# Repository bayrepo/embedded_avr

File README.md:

# embedded_avr

**Examples of code for avr controllers**

* attiny13a/uart_program - пример, как добавить передачу передачу данных с МК attiny13a по UART на скорости 9600 (пример собран c источников: https://habr.com/ru/post/250995/ и http://we.easyelectronics.ru/AVR/uart-programmnyy-na-atiny13a.html)
* attiny45/i2c_slave - пример программного i2c протокола для контроллера attiny45
* atmega8/monitor_i2c_uart - программа, по выводу информации с источников подключаемых по i2c и по UART для МК ATmega8
* attiny13a/joystyk_transmitter_attiny13a - программа для опроса джойстика и посылки информации с джойстика по радиоканалу. На основе кода https://github.com/cano64/ManchesterRF
* attiny45/joystyk_reciver_attiny45 - программа приема информации с джойстика и управление серводвигателями на сонове полученной ифнормации, на основе кода https://github.com/cano64/ManchesterRF
* atmega8/power_manager_transmitter - программа и схема передатчика управления питанием для статьи ...
* atmega8/power_manager_receiwer - программа и схема приемника управления питанием для статьи ...
* atmega8/button_on_the_interrupt - программа для Atmel Studio, где кнопка с апаратным подавлением шумов присоединяется к пину PD2 (INT0) и нажатие кнопки осуществляется по прерывнию.
* atmega8/microscope_management - программа для управления приводом стола, подсветкой микроскопа, а также схема в KiCAD и 3д-модели для принтера из которых микроскоп собирался. Интересные моменты - это обработка кнопок на основании прерываний и считывание позиции потенциометра с помощью АЦП микроконтроллера.
* attiny13a/joystyk_motor_set_angle - программа для опроса джойстика и поворота двигателей на основе позиции джойстика. Угол наклона джойстика указывает на какой угол установить моторы.
* attiny13a/joystyk_motor_set_step - программа для опроса джойстика и поворота двигателей на основе позиции джойстика. Угол наклона джойстика указывает на какой шаг повернуть моторы.
* attiny13a/joystyk_motor_set_step_smooth - программа для опроса джойстика и поворота двигателей на основе позиции джойстика. Угол наклона джойстика указывает на какой шаг повернуть моторы. Движение серводвигателей более плавное.
* nomc/load - схема без МК, схема электронной нагрузки. В проекте KiCAD схема и плата, и модели для 3Д печати
* nomc/vrv600 - схема Sven VR V600.
* nomc/cnc3018 - модели для крепления лазера к станку и вентилятора, а так же модель коробочки для установки кнопок отключения вентилятора, шпинделя и кнопки сброса станка.
* attiny26l/sven_vrv600_avr - плата переходник, для использования AVR attiny26L в sven VRV600 стабилизаторе вместо Holtek микроконтрллера
* simavr/blink_c_for_testing - прошивка для attiny13a, для симуляции в simavr
* simavr/blink_c_for_testing_libsimavr - пример прошивки для attiny13a и пример программы для исследования работы прошивки и вывод изменений на выходах микроконтроллера в vcd файл
* simavr/sven600_simulation - симуляция в simavr ранее описанной прошивки для sven600. В данном случае в симуляторе реализована подача тестового входного сигнала на АЦП и организована визуальная проверка результата с помощью файла vcd.

Более детальная информация по проектам на [сайте](http://brepo.ru/)

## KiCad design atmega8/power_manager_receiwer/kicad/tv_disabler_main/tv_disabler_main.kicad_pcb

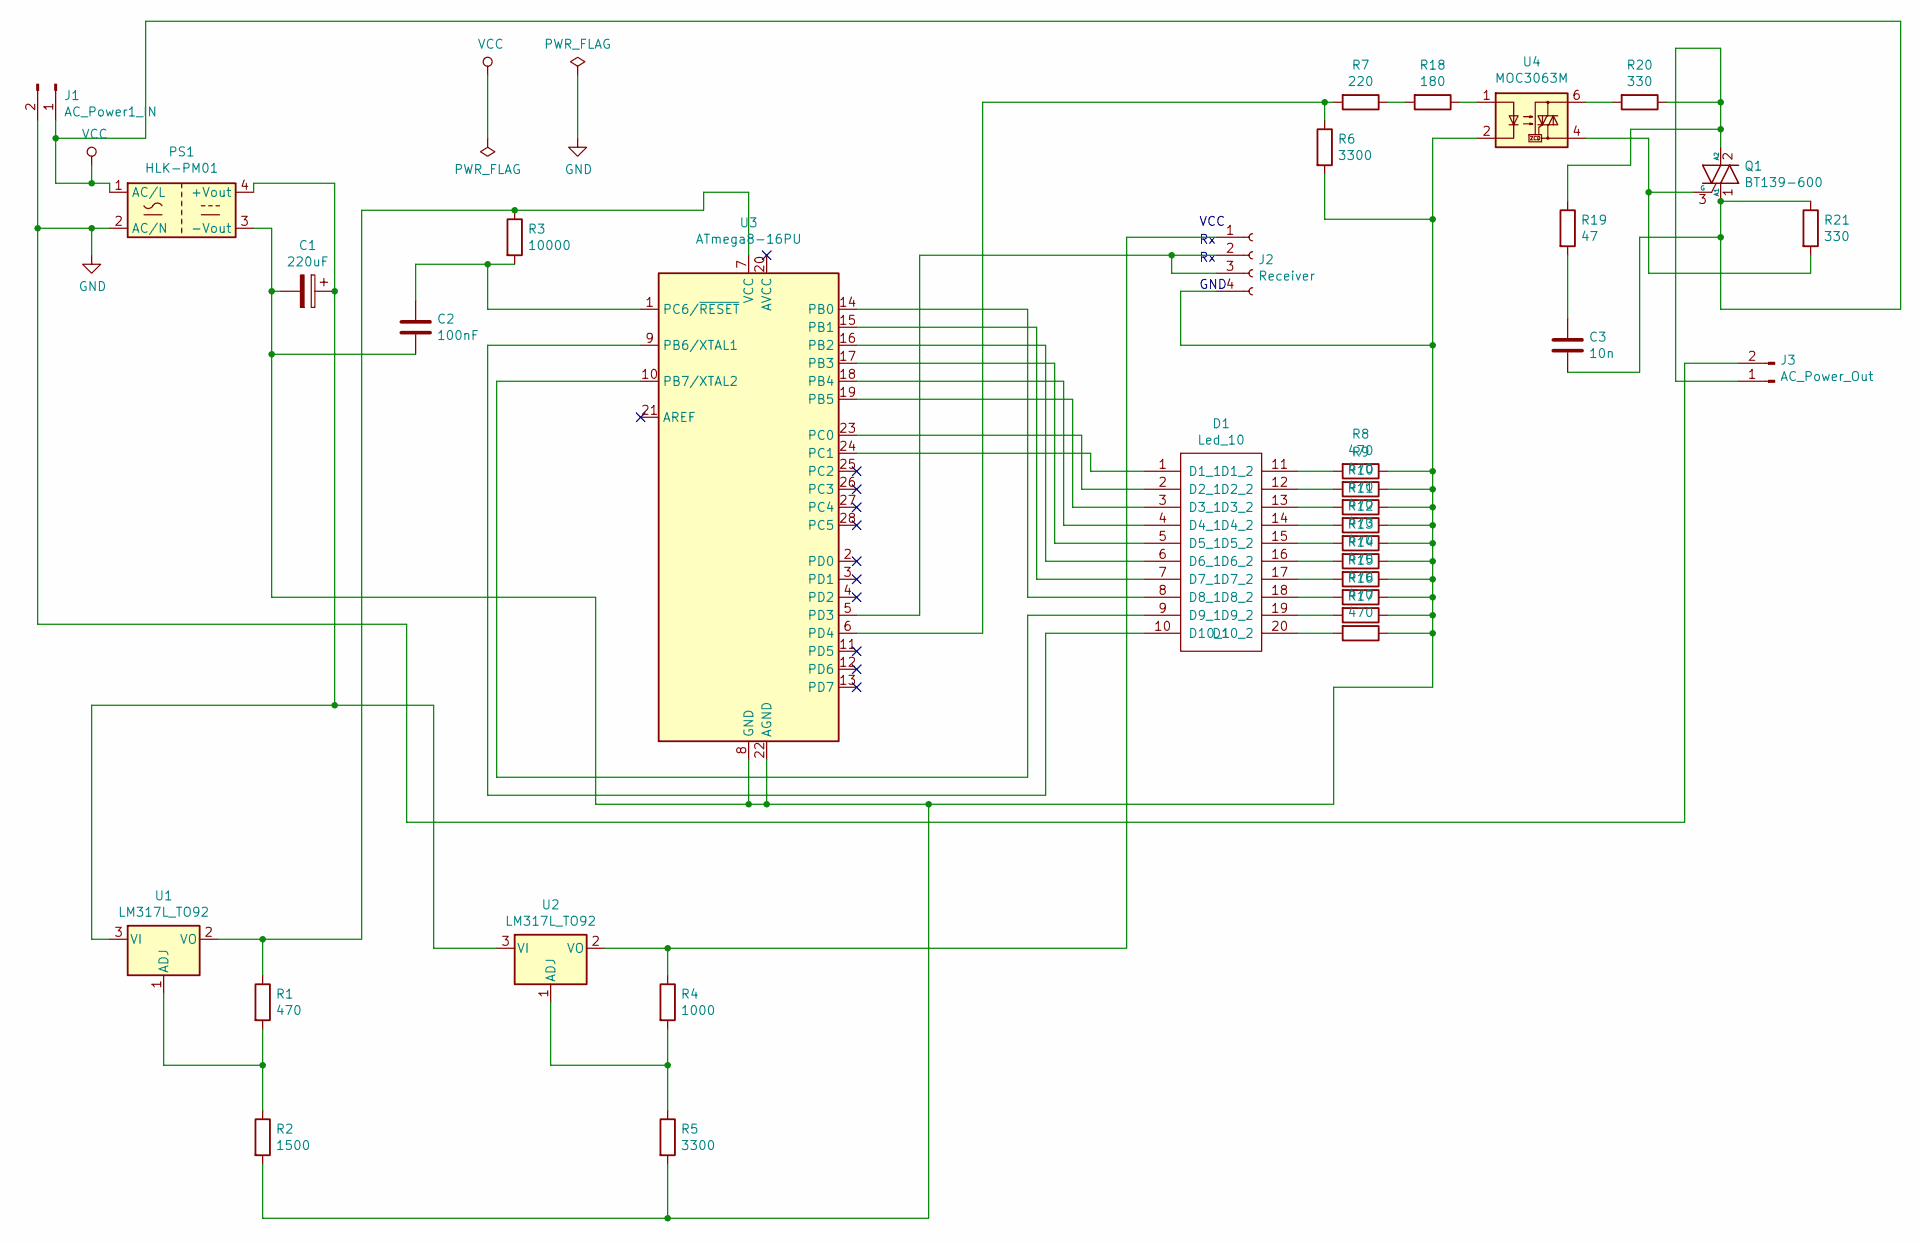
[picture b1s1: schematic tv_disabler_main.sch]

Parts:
C1: 220uF; CP_Radial_Tantal_D5.0mm_P5.00mm
C2: 100nF; C_Axial_L3.8mm_D2.6mm_P7.50mm_Horizontal
C3: 10n; C_Axial_L5.1mm_D3.1mm_P12.50mm_Horizontal
D1: Led_10; DIP-20_296_ELL
J1: AC_Power1_IN; 2-AC
J2: Receiver; SIP-4
J3: AC_Power_Out; 2-AC
PS1: HLK-PM01; ACDC-Conv_THTMeanWell-IRM-02-XX
Q1: BT139-600; TO-220-3_Vertical
R1, R8, R9, R10, R11, R12, R13, R14, R15, R16, R17: 470; R_Axial_DIN0207_L6.3mm_D2.5mm_P10.16mm_Horizontal
R2: 1500; R_Axial_DIN0207_L6.3mm_D2.5mm_P10.16mm_Horizontal
R3: 10000; R_Axial_DIN0207_L6.3mm_D2.5mm_P10.16mm_Horizontal
R4: 1000; R_Axial_DIN0207_L6.3mm_D2.5mm_P10.16mm_Horizontal
R5, R6: 3300; R_Axial_DIN0207_L6.3mm_D2.5mm_P10.16mm_Horizontal
R7: 220; R_Axial_DIN0207_L6.3mm_D2.5mm_P10.16mm_Horizontal
R18: 180; R_Axial_DIN0207_L6.3mm_D2.5mm_P10.16mm_Horizontal
R19: 47; R_Axial_Power_L50.0mm_W9.0mm_P55.88mm
R20, R21: 330; R_Axial_DIN0207_L6.3mm_D2.5mm_P10.16mm_Horizontal
U1, U2: LM317L_TO92; TO-252-2
U3: ATmega8-16PU; DIP-28_296_ELL
U4: MOC3063M; DIP-6_296_ELL

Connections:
GND: J1.2, J3.2, PS1.2 (AC/N)
unnamed: C1.1, PS1.4 (+Vout), U1.3 (VI), U2.3 (VI)
unnamed: C1.2, C2.2, J2.4, PS1.3 (-Vout), R2.2, R5.2, R6.2, R8.1, R9.1, R10.1, R11.1, R12.1, R13.1, R14.1, R15.1, R16.1, R17.1, U3.8 (GND), U3.22 (AGND), U4.2
unnamed: C2.1, R3.2, U3.1 (PC6/~RESET)
unnamed: C3.1, R19.2
unnamed: D1.1 (D1_1), U3.24 (PC1)
unnamed: D1.2 (D2_1), U3.23 (PC0)
unnamed: D1.3 (D3_1), U3.19 (PB5)
unnamed: D1.4 (D4_1), U3.18 (PB4)
unnamed: D1.5 (D5_1), U3.17 (PB3)
unnamed: D1.6 (D6_1), U3.16 (PB2)
unnamed: D1.7 (D7_1), U3.15 (PB1)
unnamed: D1.8 (D8_1), U3.14 (PB0)
unnamed: D1.9 (D9_1), U3.10 (PB7/XTAL2)
unnamed: D1.10 (D10_1), U3.9 (PB6/XTAL1)
unnamed: D1.11 (D1_2), R8.2
unnamed: D1.12 (D2_2), R9.2
unnamed: D1.13 (D3_2), R10.2
unnamed: D1.14 (D4_2), R11.2
unnamed: D1.15 (D5_2), R12.2
unnamed: D1.16 (D6_2), R13.2
unnamed: D1.17 (D7_2), R14.2
unnamed: D1.18 (D8_2), R15.2
unnamed: D1.19 (D9_2), R16.2
unnamed: D1.20 (D10_2), R17.2
unnamed: J2.1, R4.1, U2.2 (VO)
unnamed: J2.2, J2.3, U3.5 (PD3)
unnamed: J3.1, Q1.2 (A2), R19.1, R20.1
unnamed: Q1.3 (G), R21.2, U4.4
unnamed: R1.1, R3.1, U1.2 (VO), U3.7 (VCC)
unnamed: R1.2, R2.1, U1.1 (ADJ)
unnamed: R4.2, R5.1, U2.1 (ADJ)
unnamed: R6.1, R7.2, U3.6 (PD4)
unnamed: R18.1, U4.1
unnamed: R7.1, R18.2
unnamed: R20.2, U4.6
VCC: C3.2, J1.1, PS1.1 (AC/L), Q1.1 (A1), R21.1

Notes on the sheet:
VCC
GND

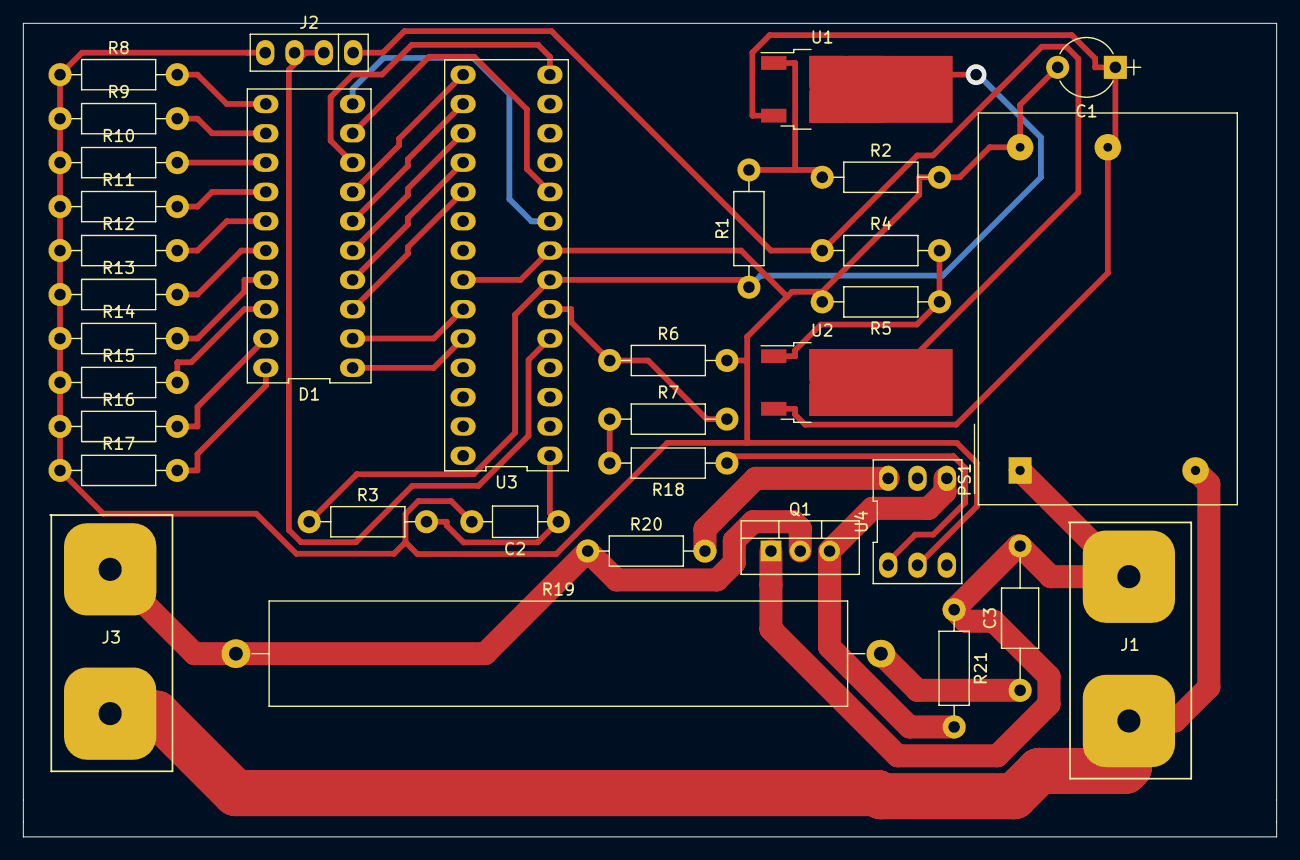
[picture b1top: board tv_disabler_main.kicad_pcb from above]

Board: 2 copper layers, 108.6 x 70.5 mm, 34 parts (0 on the bottom side), 37 nets.

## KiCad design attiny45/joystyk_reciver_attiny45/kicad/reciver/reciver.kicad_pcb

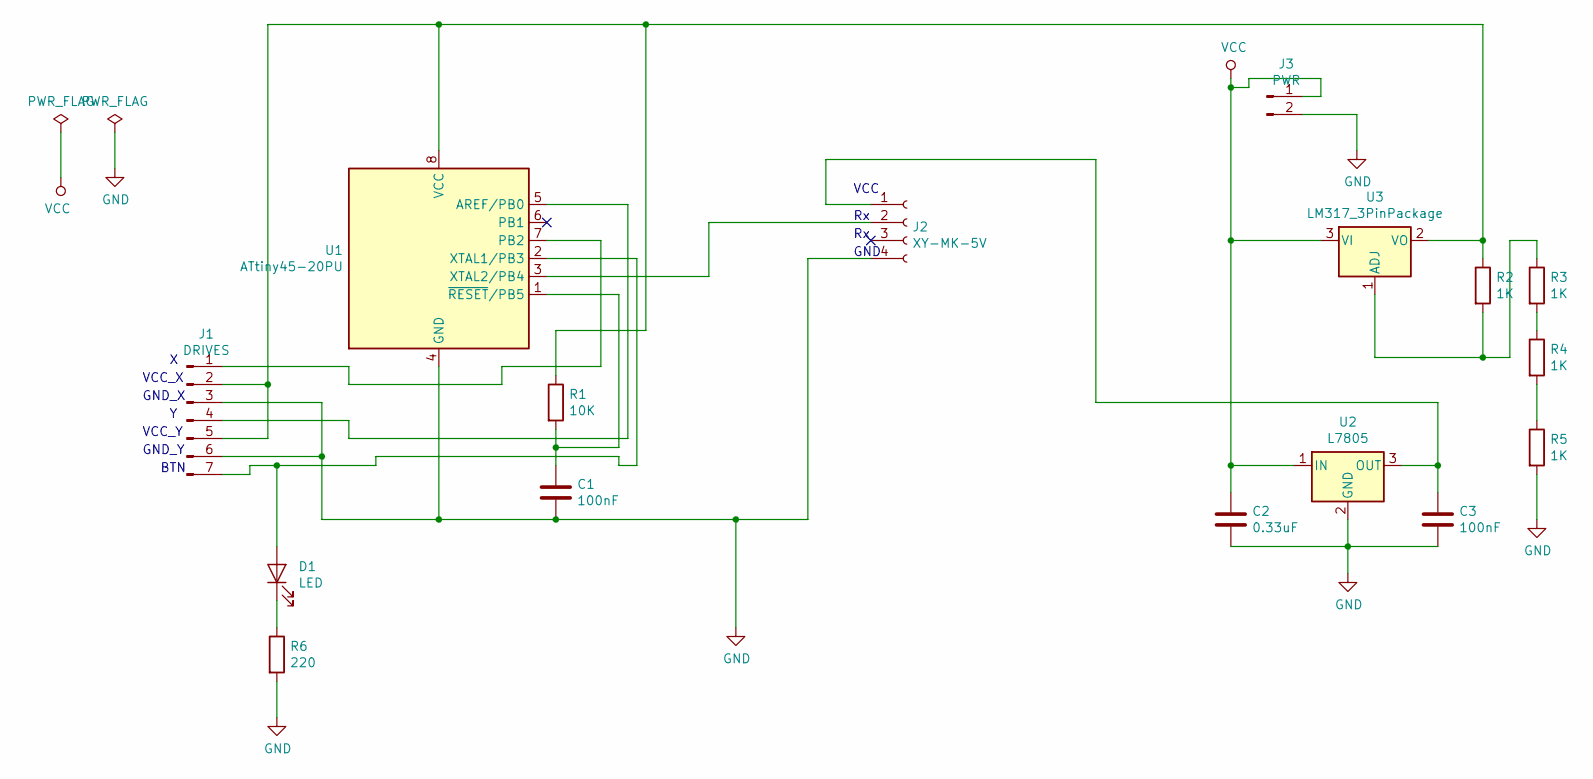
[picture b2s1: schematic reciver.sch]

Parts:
C1, C3: 100nF; R_my_5_08
C2: 0.33uF; R_my_5_08
D1: LED; R_my_5_08
J1: DRIVES; Socket_My_7_Pitch2.54mm
J2: XY-MK-5V; Socket_Strip_Straight_1x04_Pitch2.54mm
J3: PWR; Socket_2_My
R1: 10K; R_my_5_08
R2, R3, R4, R5: 1K; R_my_5_08
R6: 220; R_my_5_08
U1: ATtiny45-20PU; DIP-8_296
U2: L7805; Socket_3_My
U3: LM317_3PinPackage; Socket_3_My

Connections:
GND: C1.2, C2.2, C3.2, J1.3, J1.6, J2.4, J3.2, R5.2, R6.2, U1.4 (GND), U2.2 (GND)
unnamed: C1.1, R1.2, U1.1 (~RESET~/PB5)
unnamed: C3.1, J2.1, U2.3 (OUT)
unnamed: D1.1 (K), R6.1
unnamed: D1.2 (A), J1.7, U1.2 (XTAL1/PB3)
unnamed: J1.1, U1.7 (PB2)
unnamed: J1.2, J1.5, R1.1, R2.1, U1.8 (VCC), U3.2 (VO)
unnamed: J1.4, U1.5 (AREF/PB0)
unnamed: J2.2, U1.3 (XTAL2/PB4)
unnamed: R2.2, R3.1, U3.1 (ADJ)
unnamed: R3.2, R4.1
unnamed: R4.2, R5.1
VCC: C2.1, J3.1, U2.1 (IN), U3.3 (VI)

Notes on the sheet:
VCC
GND
VCC_X
GND_X
VCC_Y
GND_Y
BTN

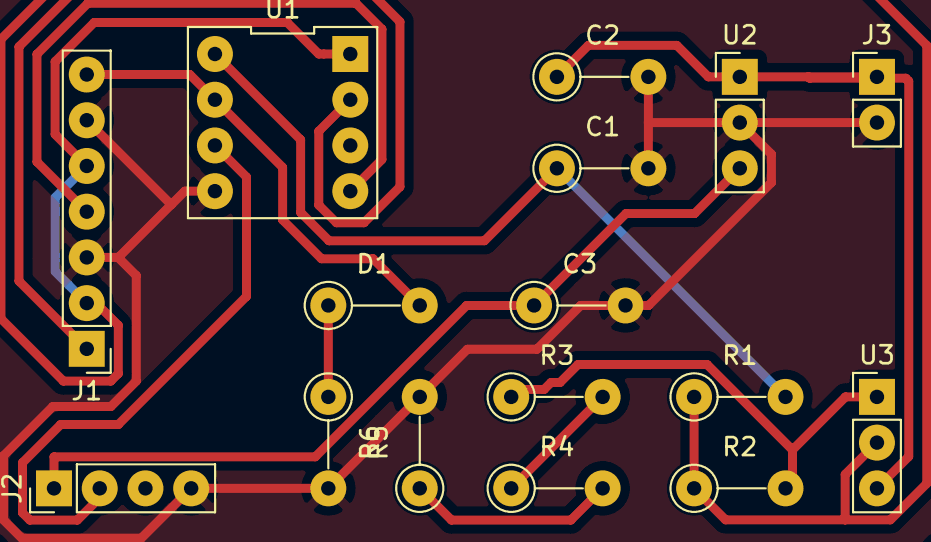
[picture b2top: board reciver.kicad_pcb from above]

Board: 2 copper layers, 16 parts (0 on the bottom side), 13 nets.

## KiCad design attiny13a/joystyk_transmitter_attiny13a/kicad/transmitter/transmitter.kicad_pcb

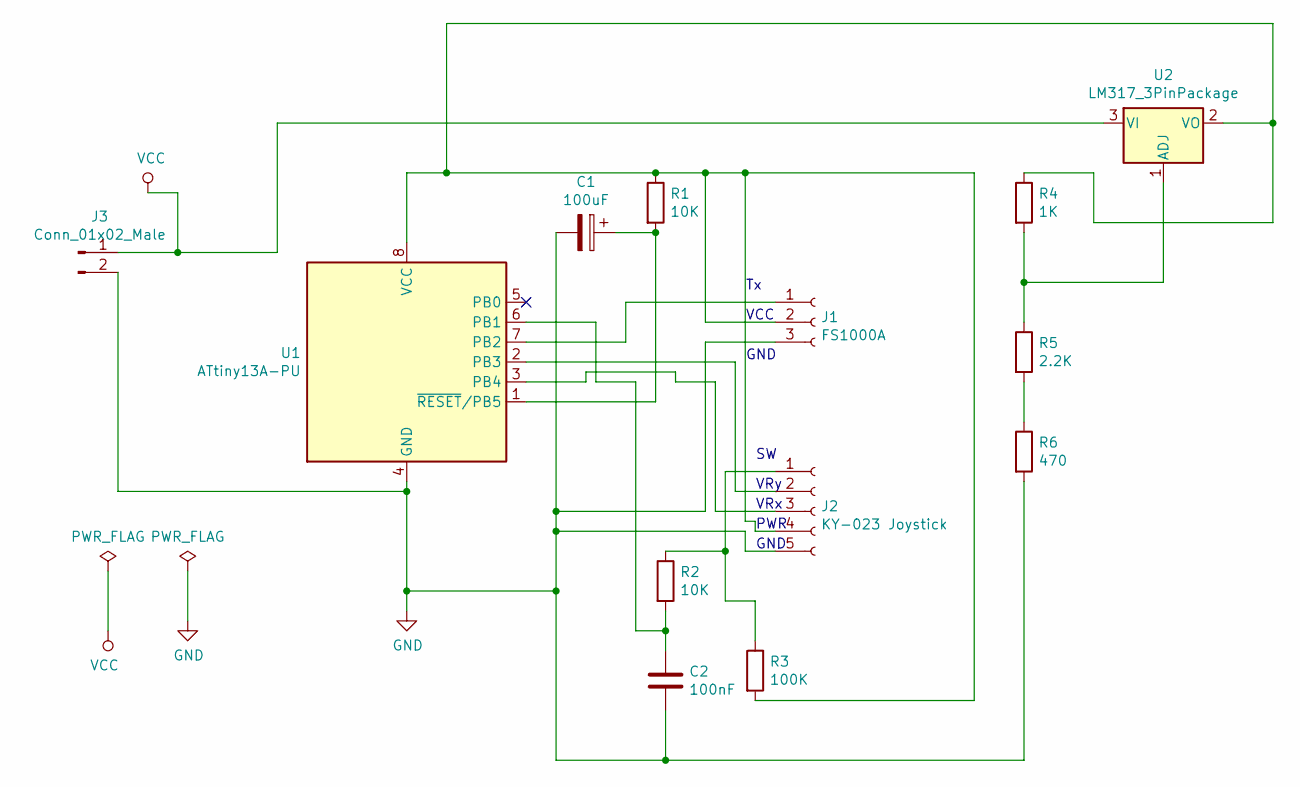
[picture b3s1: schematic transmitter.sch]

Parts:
C1: 100uF; CP_My
C2: 100nF; R_my_5_08
J1: FS1000A; Socket_3_My
J2: KY-023 Joystick; Socket_5_My
J3: Conn_01x02_Male; Socket_2_My
R1, R2: 10K; R_my_5_08
R3: 100K; R_my_5_08
R4: 1K; R_my_5_08
R5: 2.2K; R_my_5_08
R6: 470; R_my_5_08
U1: ATtiny13A-PU; DIP-8_296
U2: LM317_3PinPackage; Socket_3_My

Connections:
GND: C1.2, C2.2, J1.3, J2.5, J3.2, R6.2, U1.4 (GND)
unnamed: C1.1, R1.2, U1.1 (~RESET~/PB5)
unnamed: C2.1, R2.2, U1.6 (PB1)
unnamed: J1.1, U1.7 (PB2)
unnamed: J1.2, J2.4, R1.1, R3.2, R4.1, U1.8 (VCC), U2.2 (VO)
unnamed: J2.1, R2.1, R3.1
unnamed: J2.2, U1.2 (PB3)
unnamed: J2.3, U1.3 (PB4)
unnamed: R4.2, R5.1, U2.1 (ADJ)
unnamed: R5.2, R6.1
VCC: J3.1, U2.3 (VI)

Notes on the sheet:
VCC
GND
VRy
VRx
PWR

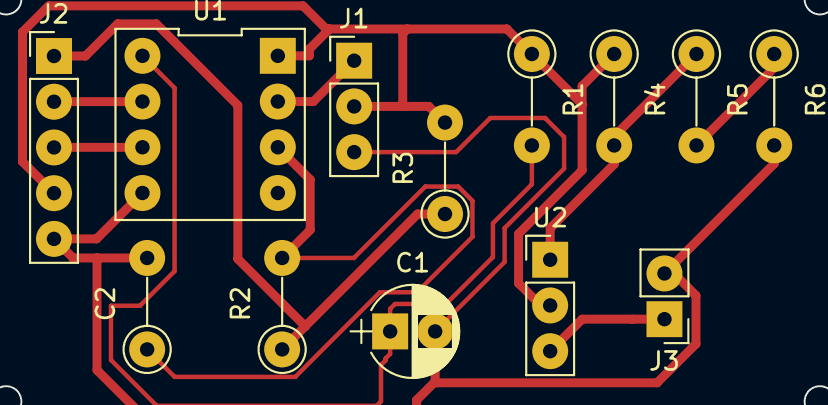
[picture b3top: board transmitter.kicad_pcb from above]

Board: 2 copper layers, 13 parts (0 on the bottom side), 11 nets.

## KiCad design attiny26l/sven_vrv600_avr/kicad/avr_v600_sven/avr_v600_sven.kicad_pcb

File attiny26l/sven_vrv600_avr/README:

В составе проекта:
main.c - исходный код программы, для МК attiny26L
stimuli_converter - в папке расположен питон скрипт, для преобразования csv файла, полученного на логическом аанализаторе LA1010
для запуска конвертера используется команда:
python3 conver2.py 8000000 2021-02-03_00-59-54_0_scl_1_sda.csv test.stim 10
где python3 conver2.py [частота в герцах] [файл csv] [выходной стимули файл] [число холостых тактов, когда начальные значения не менялись]

Пример csv файла:
Time[s],  PINB 2,  PINB 0, PINA 7
-0.012501375, 0, 1, 0
0.000000000, 1, 1, 0
0.000010250, 1, 0, 0
0.000020125, 0, 0, 0
0.000021000, 0, 1, 0
0.000028625, 0, 0, 0
0.000037875, 1, 0, 0
0.000047375, 0, 0, 1
0.000057250, 1, 0, 0
0.000066625, 0, 0, 0
Файл полученный от экспорта LA1010, в первой строке должен быть дополнен номерами пинов МК, на которые сигнал будет подан
т.е PINB 2 - это PINB МК его третий бит, PINB 0 - первый бит и т.д. Пины могут быть разные.

Пример запуска:
$ python3 conver2.py 8000000 test1.csv test1_out.stim 10
F_CPU 8000000 from file test1.csv
1 cyckle size 0.000000125000

tests - папка с тестами и моделированием:

1 - моделирование функции getWaveMax, вычисление максимального значения на положительной полуволне:
$ ./sven600
Test 1. One wave 0=T(U) 10=T(U) 20=T(U) 30=T(U) 310=T(U) 320=T(U) 340=T(U) 310=T(U) 300=T(340) 100=T(U) 40=T(U) 20=T(U) 0=T(U) 0=T(U) 
Test 2. One distorted wave 0=T(U) 10=T(U) 20=T(U) 30=T(U) 310=T(U) 320=T(U) 340=T(U) 310=T(U) 320=T(U) 330=T(U) 320=T(U) 310=T(U) 100=T(340) 0=T(U) 
Test 3. One dist wave second huge 0=T(U) 10=T(U) 20=T(U) 30=T(U) 310=T(U) 320=T(U) 340=T(U) 310=T(U) 320=T(U) 330=T(U) 340=T(U) 350=T(U) 320=T(U) 310=T(U) 100=T(350) 0=T(U) 
Test 4. Two waves 0=T(U) 10=T(U) 20=T(U) 30=T(U) 310=T(U) 320=T(U) 340=T(U) 310=T(U) 290=T(340) 330=T(U) 330=T(U) 325=T(U) 320=T(U) 310=T(U) 100=T(330) 0=T(U) 
Test 5 340 == 340. One wave
Test 6 340 == 340. One distorted wave
Test 7 350 == 350. One dist wave second huge
Test 8 330 == 330. Two waves, check both
Test 9 340 == 340. Two waves, check only first
Test 10. A lot of small waves 100=T(U) 350=T(U) 100=T(U) 350=T(U) 100=T(U) 350=T(U) 100=T(U) 350=T(U) 100=T(U) 350=T(U) 100=T(U) 350=T(U) 100=T(U) 350=T(U) 100=T(U) 
Test 11. A lot of small waves 2 100=T(U) 350=T(U) 350=T(U) 100=T(350) 350=T(U) 350=T(U) 100=T(350) 350=T(U) 350=T(U) 100=T(350) 350=T(U) 350=T(U) 100=T(350)

2 - моделирование перехода между состояниями getLimit, при различных значениях на LineIn:
$ ./sven600_2
0) Volt UNDEF=63
1) Volt UNDEF=79
2) Volt UNDEF=99
3) Volt UNDEF=107
4) Volt UNDEF=158
5) Volt UNDEF=177
6) Volt UNDEF=142
7) Volt UNDEF=101
8) Volt 177 cond 0
9) Volt UNDEF=31
10) Volt UNDEF=63
11) Volt UNDEF=79
12) Volt UNDEF=99
13) Volt UNDEF=107
14) Volt UNDEF=158
15) Volt UNDEF=179
16) Volt UNDEF=142
17) Volt UNDEF=101
18) Volt 179 cond 1
19) Volt UNDEF=31
20) Volt UNDEF=63
21) Volt UNDEF=79
22) Volt UNDEF=99
23) Volt UNDEF=107
24) Volt UNDEF=158
25) Volt UNDEF=175
26) Volt UNDEF=142
27) Volt UNDEF=101
28) Volt 175 cond 1
29) Volt UNDEF=31
30) Volt UNDEF=63
31) Volt UNDEF=79
32) Volt UNDEF=99
33) Volt UNDEF=107
34) Volt UNDEF=158
35) Volt UNDEF=170
36) Volt UNDEF=142
37) Volt UNDEF=101
38) Volt 170 cond 0
39) Volt UNDEF=31
40) Volt UNDEF=63
41) Volt UNDEF=79
42) Volt UNDEF=99
43) Volt UNDEF=107
44) Volt UNDEF=158
45) Volt UNDEF=177
46) Volt UNDEF=142
47) Volt UNDEF=101
48) Volt 177 cond 0
49) Volt UNDEF=31
50) Volt UNDEF=63
51) Volt UNDEF=79
52) Volt UNDEF=99
53) Volt UNDEF=107
54) Volt UNDEF=158
55) Volt UNDEF=205
56) Volt UNDEF=142
57) Volt UNDEF=101
58) Volt 205 cond 2
59) Volt UNDEF=31
60) Volt UNDEF=63
61) Volt UNDEF=79
62) Volt UNDEF=99
63) Volt UNDEF=107
64) Volt UNDEF=158
65) Volt UNDEF=201
66) Volt UNDEF=142
67) Volt UNDEF=101
68) Volt 201 cond 2
69) Volt UNDEF=31
70) Volt UNDEF=63
71) Volt UNDEF=79
72) Volt UNDEF=99
73) Volt UNDEF=107
74) Volt UNDEF=158
75) Volt UNDEF=205
76) Volt UNDEF=142
77) Volt UNDEF=101
78) Volt 205 cond 2
79) Volt UNDEF=31
80) Volt UNDEF=63
81) Volt UNDEF=79
82) Volt UNDEF=99
83) Volt UNDEF=107
84) Volt UNDEF=158
85) Volt UNDEF=189
86) Volt UNDEF=142
87) Volt UNDEF=101
88) Volt 189 cond 1
89) Volt UNDEF=31

3 - эксперимент, когда getWaveMax возвращает не максимальное, а усредненное значение (алгоритм от которого я решил отказаться)
$ ./sven600_3
Test 1. One wave 0=T(U) 10=T(U) 20=T(U) 30=T(U) 310=T(U) 320=T(U) 340=T(U) 310=T(U) 300=T(318) 100=T(U) 40=T(U) 20=T(U) 0=T(U) 0=T(U) 
Test 2. One distorted wave 0=T(U) 10=T(U) 20=T(U) 30=T(U) 310=T(U) 320=T(U) 340=T(U) 310=T(U) 320=T(U) 330=T(U) 320=T(U) 310=T(U) 100=T(316) 0=T(U) 
Test 3. One dist wave second huge 0=T(U) 10=T(U) 20=T(U) 30=T(U) 310=T(U) 320=T(U) 340=T(U) 310=T(U) 320=T(U) 330=T(U) 340=T(U) 350=T(U) 320=T(U) 310=T(U) 100=T(320) 0=T(U) 
Test 4. Two waves 0=T(U) 10=T(U) 20=T(U) 30=T(U) 310=T(U) 320=T(U) 340=T(U) 310=T(U) 290=T(318) 330=T(U) 330=T(U) 325=T(U) 320=T(U) 310=T(U) 100=T(316) 0=T(U) 
Test 5 318 == 340. One wave
Test 6 316 == 340. One distorted wave
Test 7 320 == 350. One dist wave second huge
Test 8 316 == 330. Two waves, check both
Test 9 318 == 340. Two waves, check only first
Test 10. A lot of small waves 100=T(U) 350=T(U) 100=T(U) 350=T(U) 100=T(U) 350=T(U) 100=T(U) 350=T(U) 100=T(U) 350=T(U) 100=T(U) 350=T(U) 100=T(U) 350=T(U) 100=T(U) 
Test 11. A lot of small waves 2 100=T(U) 350=T(U) 350=T(U) 100=T(350) 350=T(U) 350=T(U) 100=T(350) 350=T(U) 350=T(U) 100=T(350) 350=T(U) 350=T(U) 100=T(350)

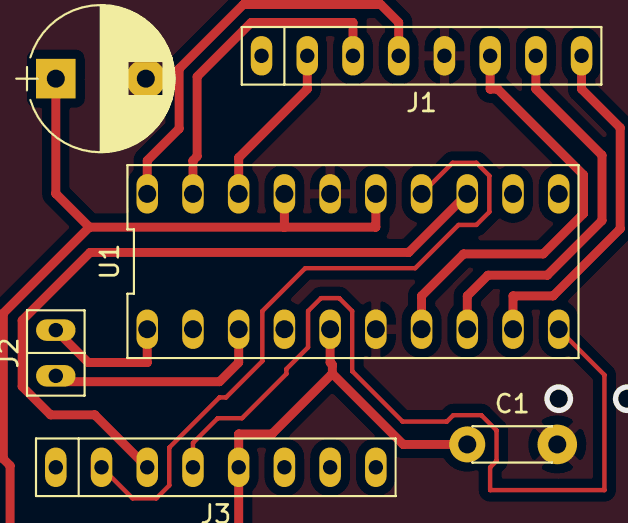
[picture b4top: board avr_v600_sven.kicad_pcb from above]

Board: 2 copper layers, 6 parts (0 on the bottom side), 13 nets.

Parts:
C1: 100nF; C_Disc_D4.3mm_W1.9mm_P5.00mm
C2: 100uF; CP_Radial_D8.0mm_P5.00mm
J1: Left_Line; SIP-8
J2: Debug_Pins; SIP-2
J3: Right_Line; SIP-8
U1: ATtiny26L-8PU; DIP-20_296_ELL

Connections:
GND: C1.2, C2.2, J1.5, U1.6, U1.16
unnamed: J1.2, U1.18
unnamed: J1.3, U1.19
unnamed: J1.4, U1.20
unnamed: J1.6, U1.7
unnamed: J1.7, U1.8
unnamed: J1.8, U1.9
unnamed: J2.1, U1.1
unnamed: J2.2, U1.3
unnamed: J3.2, U1.14
unnamed: J3.3, U1.13
unnamed: J3.4, U1.10
VCC: C1.1, C2.1, J3.5, U1.5, U1.15, U1.17

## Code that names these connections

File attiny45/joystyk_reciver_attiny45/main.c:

/*
* radio_recv_attiny45_85.c
*
* Created: 04.12.2019 22:54:17
* Author : bayre
*/

#include <avr/io.h>
#include "ManchesterRF.h"
#include <avr/delay.h>
#include <string.h>
#include <avr/interrupt.h>

#define MAGIC_NUMBER 0xFFEE
#define MESSAGE_SIZE 4
int X_coord = 0;
int Y_coord = 0;
unsigned char button = 0;

unsigned char X_p = 0;
unsigned char Y_p = 0;

uint16_t *tmpData;
unsigned char *tmpBuffer;
unsigned char rxSize;
unsigned char bufferData[sizeof(uint16_t) * MESSAGE_SIZE];
unsigned char last_index;
unsigned char magic_found = 0;

#ifdef DEBUG_S
//ATtiny45 8000000
void ddelay_ms(int ms){
	int ms1=F_CPU/1000 - 1600;
	unsigned char bt = 0;
	int ms2 = 0;
	for(bt=0; bt<ms; bt++){
		for(ms2=0;ms2<(ms1>>2);ms2++){
			asm volatile ("mov r0, r0");
		}
	}
}

void ddelay_us(int us){
	int ms1=F_CPU/1000000 - 4;
	unsigned int bt = 0;
	int ms2 = 0;
	if (us<10) return;
	for(bt=0; bt<us; bt++){
		for(ms2=0;ms2<(ms1>>1);ms2++){
			asm volatile ("mov r0, r0");
		}
	}
}
#endif

#define HZ50_CKL 156//312
#define HZ50_CENTER 12//23
#define HZ50_LEFT 17//33
#define HZ50_RIGHT 7//13
#define ADC_TOCOUNTER 100 //1023/10
static int motor_counter = 0;
static int xTranslate = 0;
static int yTranslate = 0; 
unsigned char xMoto_level = 0;
unsigned char yMoto_level = 0;
unsigned char freeze = 0;
unsigned char wait_freeze = 0;
static int waitCounter = 0;

void f_interruptor(){
    if (freeze == 0) {
        if (X_coord>=500 && X_coord<=520){
            xTranslate = 510 / ADC_TOCOUNTER;
        } else {
            xTranslate = X_coord / ADC_TOCOUNTER;
        }
        if (Y_coord>=486 && Y_coord<=506){
            yTranslate = 500 / ADC_TOCOUNTER;
            } else {
            yTranslate = Y_coord / ADC_TOCOUNTER;
        }
        xTranslate = HZ50_LEFT - xTranslate;
        yTranslate = HZ50_LEFT - yTranslate;
    }    
    if (button == 1){
        PORTB ^= (1<<PB3);
        if (PORTB & (1<<PB3)){
            freeze = 0;
            wait_freeze = 1;
            waitCounter = 0;
        } else {
            freeze = 0;
            wait_freeze = 0;
        }
        button = 0;
    }
    motor_counter++;
    if (motor_counter>=HZ50_CKL){
        motor_counter = 0;
    }
    if (!motor_counter){
        PORTB |= ((1<<PB0) | (1<<PB2));
        xMoto_level = 1;
        yMoto_level = 1;
    }
    if (motor_counter==xTranslate && xMoto_level==1){
        PORTB &= ~(1<<PB2);
        xMoto_level = 0;
    }
    if (motor_counter==yTranslate && yMoto_level==1){
        PORTB &= ~(1<<PB0);
        yMoto_level = 0;
    }
    if (wait_freeze == 1) {
        waitCounter++;
        if (waitCounter == 15625){
            freeze = 1;
            wait_freeze = 0;
        }
    }
}

int main(void){
	DDRB |= (1 << PB1) | (1 << PB0) | (1<<PB2) | (1<<PB3);
	PORTB &= ~((1<<PB1) | (1<<PB0)|(1<<PB2)|(1<<PB3));
	tmpData = (uint16_t *)bufferData;
	char index = 0;
    X_coord = 510;
    Y_coord = 496;
    ManchesterRF_setFunction(&f_interruptor);
	ManchesterRF(MAN_1200);
	ManchesterRF_RXInit(2, _BV(PB4));
	ManchesterRF_beginReceive();
	sei();
#ifdef DEBUG_S
  //  ddelay_ms(10);
#else
    _delay_ms(10);
#endif // DEBUG_S
	while (1)
	{
		int av = ManchesterRF_available();
		if(av){
			if(ManchesterRF_receiveArray((uint8_t *)&rxSize, (uint8_t **)&tmpBuffer)){
				if (rxSize>0){
					for(index=0; index<(sizeof(uint16_t) * MESSAGE_SIZE); index++){
                        bufferData[index] = tmpBuffer[index];
                    }
					if ((tmpData[0] == MAGIC_NUMBER) && (tmpData[1]>=0 && tmpData[1]<=1023) && (tmpData[2]>=0 && tmpData[2]<=1023) && (tmpData[3]>=0 && tmpData[3]<=1)){
									X_coord = tmpData[1];
									Y_coord = tmpData[2];
									button = (unsigned char)tmpData[3];
					}
								
				}
			}
		}
		#ifdef DEBUG_S
		ddelay_ms(5);
		#else
		_delay_ms(5);
		#endif // DEBUG_S
	}
	return 0;
}

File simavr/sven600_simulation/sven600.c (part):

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#define _BV(bit) (1 << (bit))

//Pins
#define RELE3 PB4
#define RELE2 PB5
#define RELE1 PB6
#define RED_LIGHT PA4
#define YELLOW_LIGHT PA5

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#define DDR_USI             DDRB
#define PORT_USI            PORTB
#define PIN_USI             PINB
#define PORT_USI_SDA        PB0
#define PORT_USI_SCL        PB2
#define PIN_USI_SDA         PINB0
#define PIN_USI_SCL         PINB2

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
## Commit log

2019-12-29 Test
2019-12-29 Added i2c, uart program, monitor_i2c
2019-12-30 Added information
2019-12-30 Added KiCad files
2020-01-03 Added joystick radio project
2020-01-04 Move projects to correct directory. Added URL of some source code
2020-01-06 Added license file
2020-01-06 Added transmitter kicad files
2020-01-07 Added reciver kicad
2020-01-08 Added fix to the reciever kicad schema
2020-01-19 Added freeze option
2020-01-19 Added renew recv kicad scheme
2020-02-29 Added power_manager_receiwer and power_manager_transmitter code
2020-07-08 Added file - button_on_interrupt
2020-07-08 Added missing file for button_on_the_interrupt
2020-07-31 Update README.md, keeper_far.stl, and 20 more files... Add project microscope manager - project for atmega8
2020-07-31 typo fix
2020-08-10 Added 8steps instead of 4steps
2020-08-11 Added camera holder to the microscope project
2020-10-08 Added joystyk_motor_set_angle program for manage the motors
2020-10-09 Added fix for set_angle Added joystyk_motor_set_step/main.c
2020-10-10 Added joystyk_motor_set_step_smooth/main.c
2020-10-10 Added joystyk_motor_set_step/main.c Added joystyk_motor_set_step_smooth/main.c
2020-11-27 Electronic load
2020-11-27 Added info to README.md
2021-01-06 Added vr v600 scheme
2021-02-27 Added sven600 holtek to avr convertor
2021-05-15 Added simavr simulation examples
2021-09-15 Added stl files for CNC3018 modification
